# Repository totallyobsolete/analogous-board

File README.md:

# analogous-board
The Analogous Board is a replacement for the Apple Macintosh SE and SE/30 analog board that provides mounting points for the original power supply and supporting circuitry for replacing the CRT with a VGA LCD.

It is designed to use <a href="https://github.com/guruthree/mac-se-video-converter">guruthree's mac-se-video-converter firmware for RP2040</a>.

<p xmlns:cc="http://creativecommons.org/ns#" >This work is licensed under <a href="https://creativecommons.org/licenses/by-nc-sa/4.0/?ref=chooser-v1" target="_blank" rel="license noopener noreferrer" style="display:inline-block;">CC BY-NC-SA 4.0</a></p>

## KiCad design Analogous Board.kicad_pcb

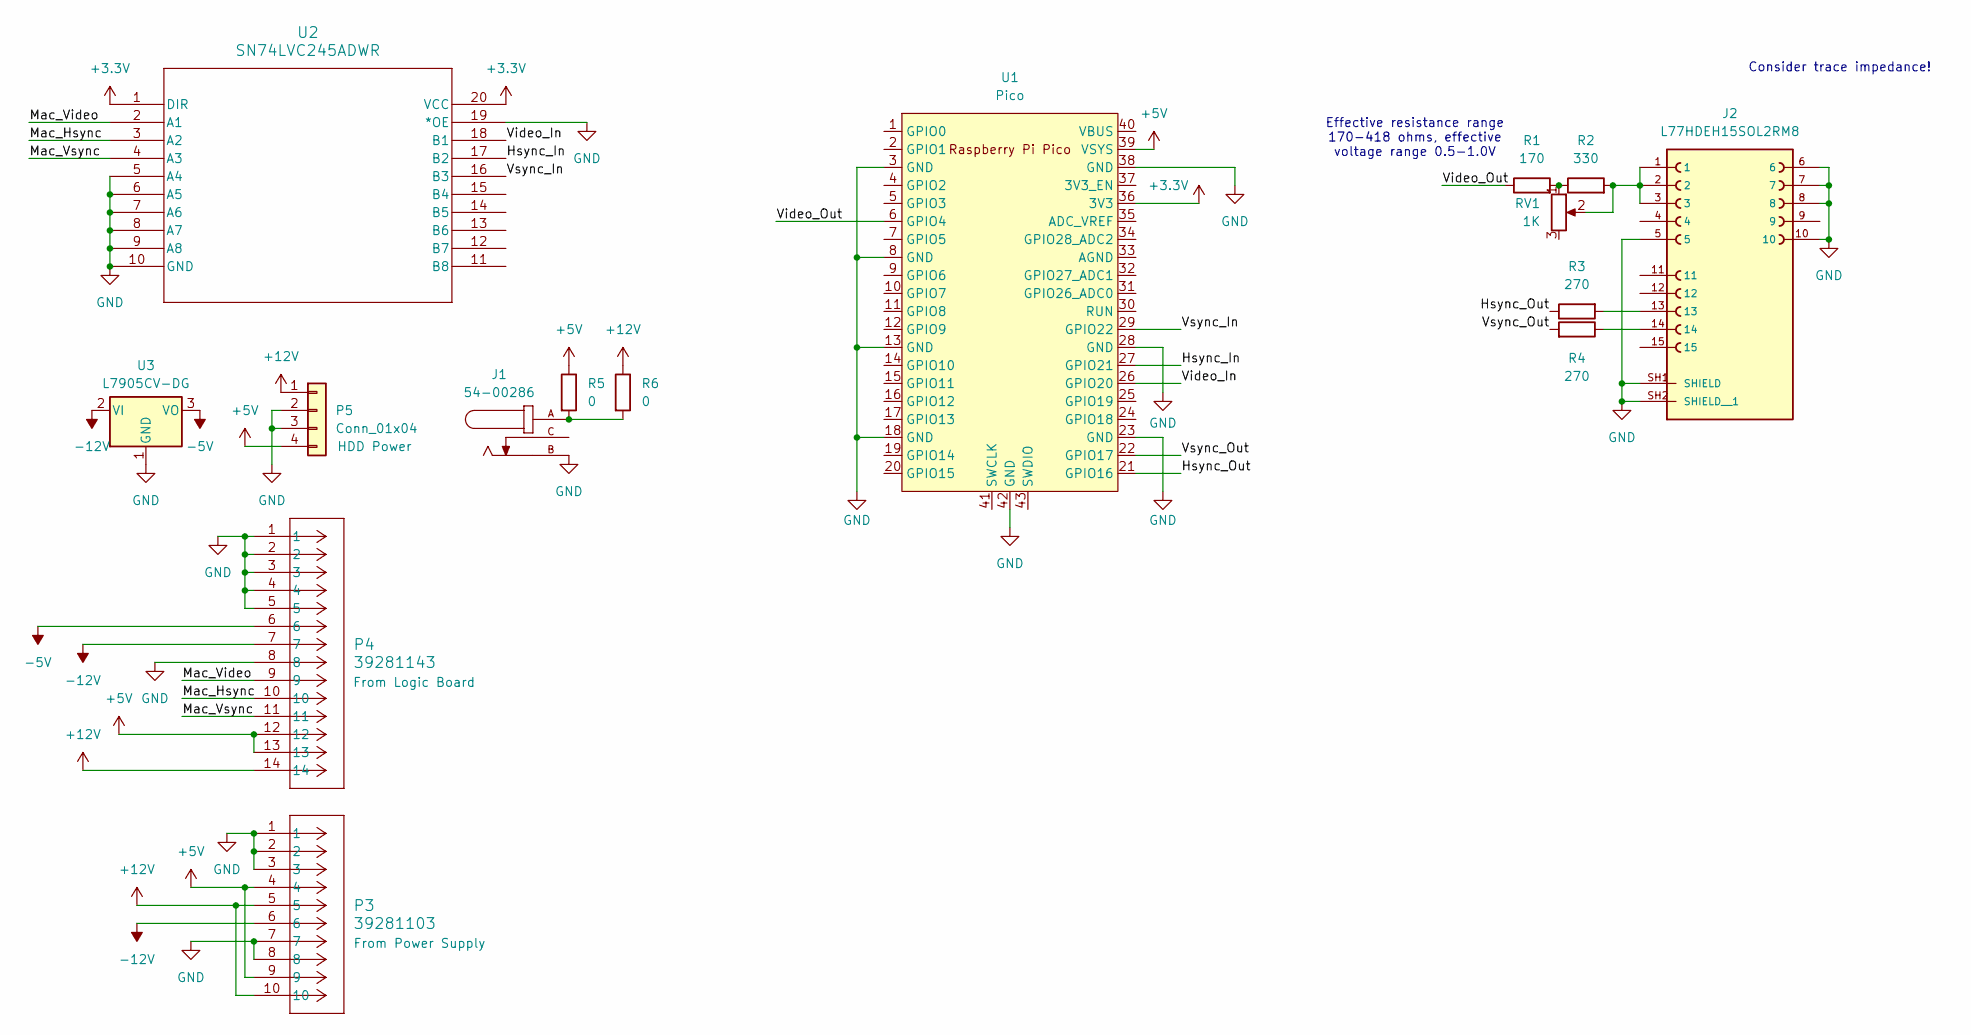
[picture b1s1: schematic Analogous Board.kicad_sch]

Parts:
J1: 54-00286; TENSILITY_54-00286; PARTREV A
J2: L77HDEH15SOL2RM8; AMPHENOL_L77HDEH15SOL2RM8; PARTREV 6
P3: 39281103; CON_39281103
P4: 39281143; CON_39281143
P5: Conn_01x04; TE_MATE-N-LOK_350211-1_1x04_P5.08mm_Vertical
R1: 170; R_0805_2012Metric_Pad1.20x1.40mm_HandSolder
R2: 330; R_0805_2012Metric_Pad1.20x1.40mm_HandSolder
R3, R4: 270; R_0805_2012Metric_Pad1.20x1.40mm_HandSolder
R5, R6: 0; R_1206_3216Metric_Pad1.30x1.75mm_HandSolder
RV1: 1K; Potentiometer_Piher_T-16H_Single_Horizontal
U1: Pico; RPi_Pico_SMD_TH
U2: SN74LVC245ADWR; DW20-M
U3: L7905CV-DG; TO-220-3_Horizontal_TabDown

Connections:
+3.3V: U1.36 (3V3), U2.1 (DIR), U2.20 (VCC)
+5V: P3.4, P3.9, P4.12, P4.13, P5.4, R5.1, U1.39 (VSYS)
+12V: P3.5, P3.10, P4.14, P5.1, R6.1
-5V: P4.6, U3.3 (VO)
-12V: P3.6, P4.7, U3.2 (VI)
/Hsync_In: U1.27 (GPIO21), U2.17 (B2)
/Hsync_Out: R3.1, U1.21 (GPIO16)
/Mac_Hsync: P4.10, U2.3 (A2)
/Mac_Video: P4.9, U2.2 (A1)
/Mac_Vsync: P4.11, U2.4 (A3)
/Video_In: U1.26 (GPIO20), U2.18 (B1)
/Video_Out: R1.1, U1.6 (GPIO4)
/Vsync_In: U1.29 (GPIO22), U2.16 (B3)
/Vsync_Out: R4.2, U1.22 (GPIO17)
GND: J1.B, J2.5, J2.6, J2.7, J2.8, J2.10, J2.SH1 (SHIELD), J2.SH2 (SHIELD__1), P3.1, P3.2, P3.3, P3.7, P3.8, P4.1, P4.2, P4.3, P4.4, P4.5, P4.8, P5.2, P5.3, U1.3 (GND), U1.8 (GND), U1.13 (GND), U1.18 (GND), U1.23 (GND), U1.28 (GND), U1.38 (GND), U1.42 (GND), U2.5 (A4), U2.6 (A5), U2.7 (A6), U2.8 (A7), U2.9 (A8), U2.10 (GND), U2.19 (*OE), U3.1 (GND)
unnamed: J1.A, R5.2, R6.2
unnamed: J2.1, J2.2, J2.3, R2.2, RV1.2
unnamed: J2.13, R3.2
unnamed: J2.14, R4.1
unnamed: R1.2, R2.1, RV1.1

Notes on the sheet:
Consider trace impedance!
Effective resistance range 170-418 ohms, effective voltage range 0.5-1.0V

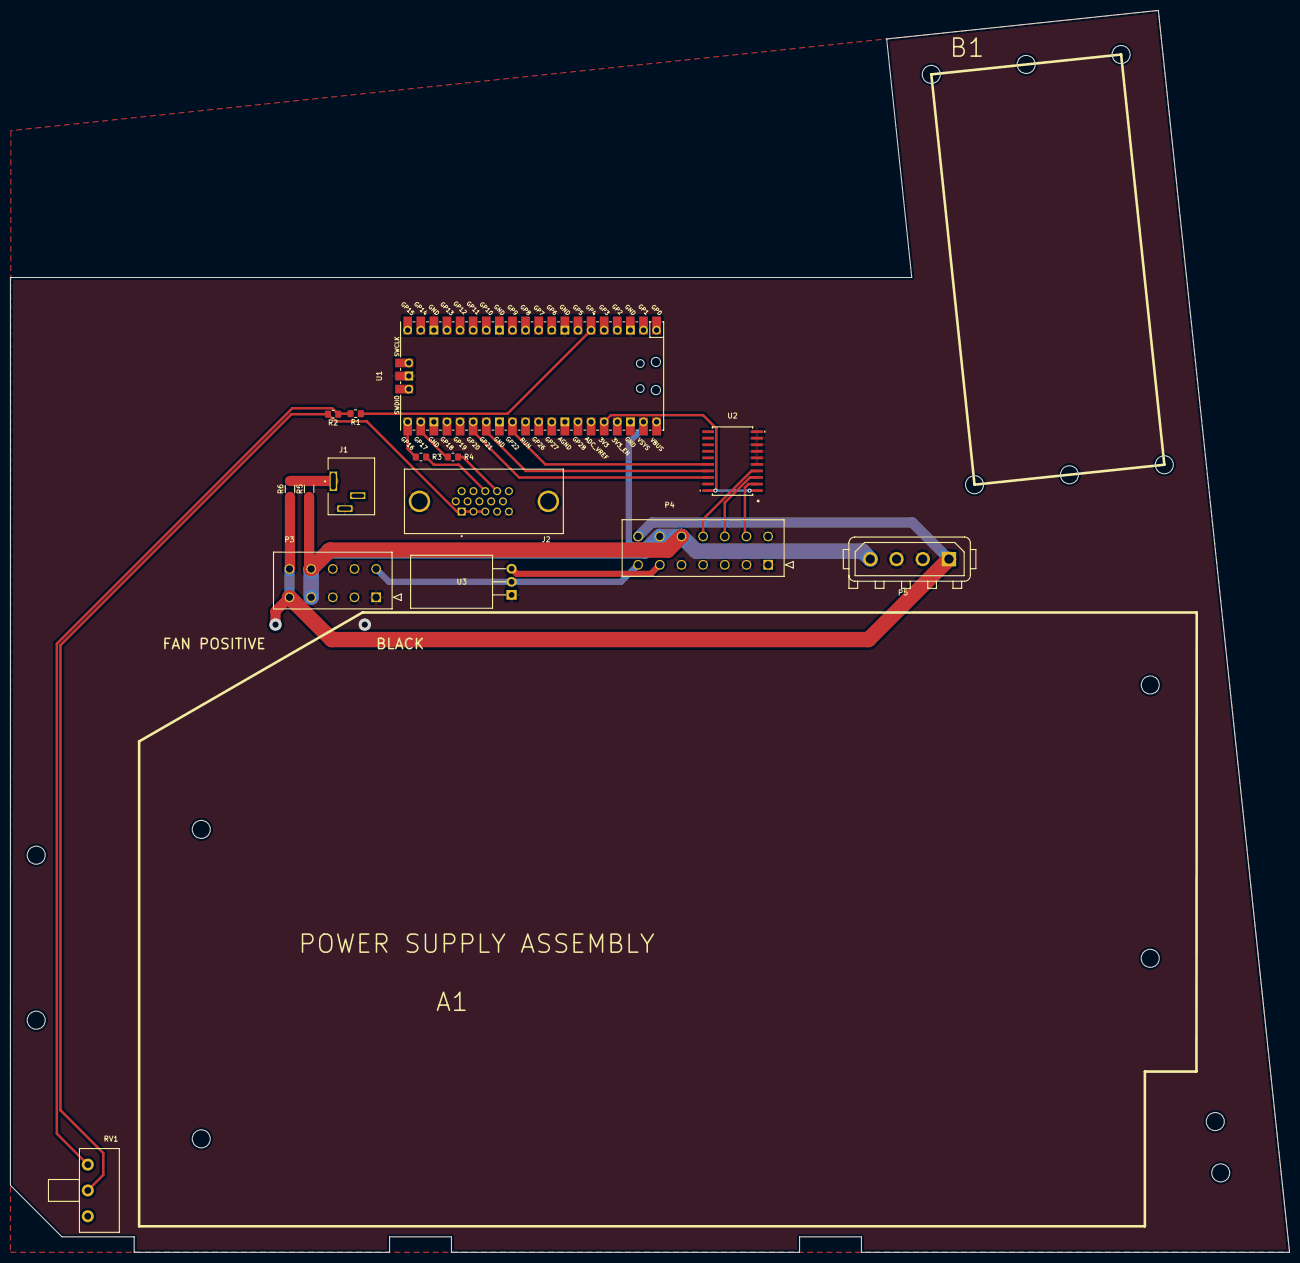
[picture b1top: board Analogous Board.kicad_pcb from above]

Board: 2 copper layers, 248.0 x 240.8 mm, 15 parts (0 on the bottom side), 20 nets.

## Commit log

2024-10-07 Create LICENSE
2024-10-07 Initial HW design
